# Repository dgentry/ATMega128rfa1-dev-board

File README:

A Better ATMega 128rfa1 Dev Board

See http://www.sparkfun.com/products/9734

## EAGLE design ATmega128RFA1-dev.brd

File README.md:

##A  Better ATMega 128rfa1 Dev Board

See http://www.sparkfun.com/products/9734

Some of the complaints in the comments that I've started to address:

1) If you solder headers into the battery (for hitec connector), ISP,
and uart pins, you won’t be able to insert the ISP programmer
connector – there isn’t any room! If you use this, put your
battery/uart headers underneath your board. A bit silly, but no other
choice.  
[Moved the ISP header left, hopefully gives enough room]

2) With nothing connected but a fully charged 6V battery, this board still has bad voltage drops when turning on the transmitter. You must solder on a capacitor between ground and 3.3V or it won’t work. I put a 20uF tantelum on it, and the resets went away.
<br>[suggested 20uF tantalum in the C5 silkscreen]

4) The traces look like someone used Eagle CAD auto-route and called it a day, without doing much of any touching up.
<br>[Reduced number of vias by about 50%, made antenna signal lines straighter and kept them on top of the board, beefed up power and ground lines where I could]

My suggestion: get rid of the power jack and then by careful redesign a similar board can be made small enough to fit in a breadboard, maybe even cheap enough for some of the people complaining about the high price tag.
<br>[to do, but not sure that'll make it super small anyway]

Oh heck, if any of you guys at SparkFun are listening, here’s my wish-list for a hypothetical future revision of this board:
1) Drop the regulator, or make it an optional DIY addition.
<br>[You're populating your own board, drop away.  :]

2) Make all of the break out pins on the top and bottom aligned to a 0.1" grid.
<br>[All the pins on the side are aligned.  The three connectors at the bottom/end of the board should probably go up, not down]

3) Add a JTAG port in addition to the ISP port. Feel free to use a 0.05" pitch connector for the JTAG port is space is tight.
<br>[to do]

4) Add a U.FL connector (or at least the landing pattern for it) to the board, so that I can solder off the chip antenna and add a Real antenna without too much headache.
<br>[to do]

The result would be a more affordable and more desirable product. I'd by another one. Or two.

Thanks to JÃ¶rg Wunsch on avrfreaks.com, the problem is that the TST
pin is left floating. After connecting this pin to ground, reset and
power on reset works reliably.
<br>[added solderable/cuttable jumper "GND-TST"]

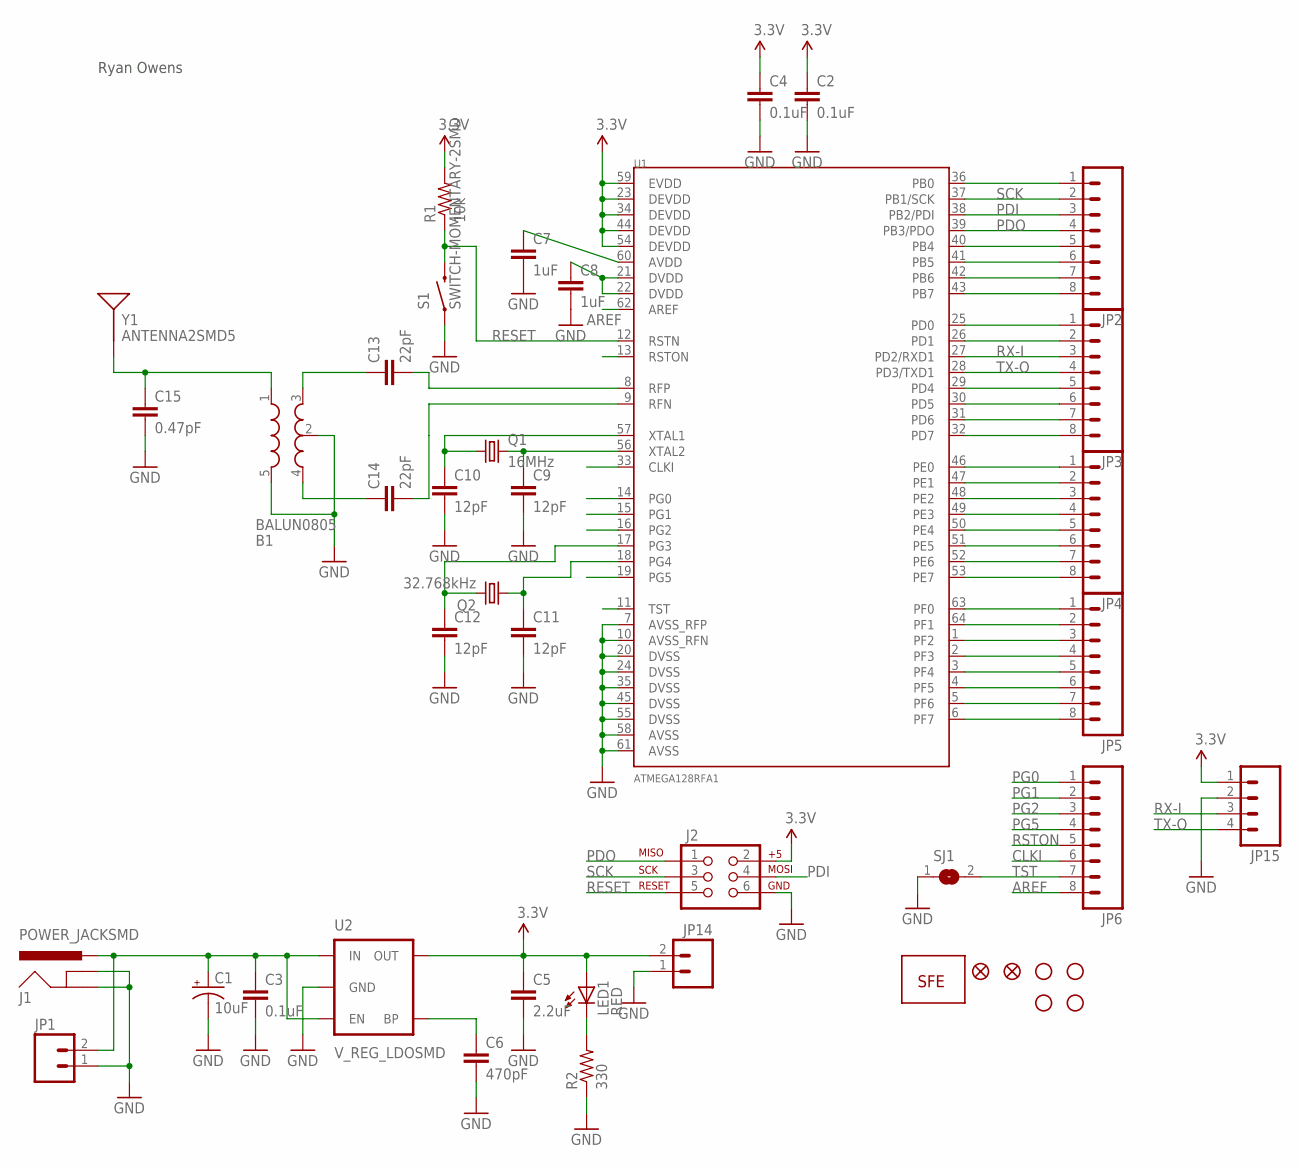
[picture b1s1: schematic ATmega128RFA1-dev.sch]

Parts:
B1: BALUN0805; BALUN
C1: 10uF; EIA3216
C2, C3, C4: 0.1uF; 0603-CAP
C5: 2.2uF; 0603-CAP
C6: 470pF; 0603-CAP
C7, C8: 1uF; 0805
C9, C10, C11, C12: 12pF; 0603-CAP
C13, C14: 22pF; 0603-CAP
C15: 0.47pF; 0603-CAP
J1: POWER_JACKSMD; POWER_JACK_SMD
J2: AVR_SPI_PRG_6PTH; 2X3
JP1, JP14: M02PTH; 1X02
JP2, JP3, JP4, JP5, JP6: M08; 1X08
JP7: LOGO-SFENEW; SFE-NEW-WEBLOGO
JP8, JP9: FIDUCIAL1X2; FIDUCIAL-1X2
JP10, JP11, JP12, JP13: STAND-OFF
JP15: M04PTH; 1X04
LED1: RED; LED-0603
Q1: 16MHz; CRYSTAL-SMD-5X3
Q2: 32.768kHz; CRYSTAL-32KHZ-SMD
R1: 10k; 0603-RES
R2: 330; 0603-RES
S1: SWITCH-MOMENTARY-2SMD; TACTILE_SWITCH_SMD
SJ1: SJ
U1: ATMEGA128RFA1; QFN-64
U2: V_REG_LDOSMD; SOT23-5
Y1: ANTENNA2SMD5; ANTENNA-CHIP5

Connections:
3.3V: C2.1, C4.1, C5.1, J2.2, JP14.2, JP15.1, LED1.A, R1.2, U1.23 (DEVDD), U1.34 (DEVDD), U1.44 (DEVDD), U1.54 (DEVDD), U1.59 (EVDD), U2.5 (OUT)
AREF: JP6.8, U1.62 (AREF)
CLKI: JP6.6, U1.33 (CLKI)
GND: B1.2 (GND), B1.5 (GND), C1.C (-), C2.2, C3.2, C4.2, C5.2, C6.2, C7.2, C8.2, C9.2, C10.2, C11.2, C12.2, C15.2, J1.GND (GNDBREAK), J1.P$4 (GND), J2.6, JP1.1, JP14.1, JP15.2, R2.1, S1.1, SJ1.1, U1.7 (AVSS_RFP), U1.10 (AVSS_RFN), U1.20 (DVSS), U1.24 (DVSS), U1.35 (DVSS), U1.45 (DVSS), U1.55 (DVSS), U1.58 (AVSS), U1.61 (AVSS), U2.2 (GND)
unnamed: B1.3 (OUT1), C13.1
unnamed: B1.4 (OUT2), C14.1
unnamed: C1.A (+), C3.1, J1.VIN0 (PWR), JP1.2, U2.1 (IN), U2.3 (EN)
unnamed: B1.1 (IN), C15.1, Y1.FEED
unnamed: C8.1, U1.21 (DVDD), U1.22 (DVDD)
unnamed: C14.2, U1.9 (RFN)
unnamed: C13.2, U1.8 (RFP)
unnamed: LED1.C, R2.2
unnamed: C7.1, U1.60 (AVDD)
unnamed: C10.1, Q1.1, U1.57 (XTAL1)
unnamed: C9.1, Q1.3 (2), U1.56 (XTAL2)
unnamed: C12.1, Q2.X2 (2), U1.17 (PG3)
unnamed: C11.1, Q2.X1 (1), U1.18 (PG4)
unnamed: C6.1, U2.4 (BP)
unnamed: JP2.1, U1.36 (PB0)
unnamed: JP2.5, U1.40 (PB4)
unnamed: JP2.6, U1.41 (PB5)
unnamed: JP2.7, U1.42 (PB6)
unnamed: JP2.8, U1.43 (PB7)
unnamed: JP3.1, U1.25 (PD0)
unnamed: JP3.2, U1.26 (PD1)
unnamed: JP3.5, U1.29 (PD4)
unnamed: JP3.6, U1.30 (PD5)
unnamed: JP3.7, U1.31 (PD6)
unnamed: JP3.8, U1.32 (PD7)
unnamed: JP4.1, U1.46 (PE0)
unnamed: JP4.2, U1.47 (PE1)
unnamed: JP4.3, U1.48 (PE2)
unnamed: JP4.4, U1.49 (PE3)
unnamed: JP4.5, U1.50 (PE4)
unnamed: JP4.6, U1.51 (PE5)
unnamed: JP4.7, U1.52 (PE6)
unnamed: JP4.8, U1.53 (PE7)
unnamed: JP5.1, U1.63 (PF0)
unnamed: JP5.2, U1.64 (PF1)
unnamed: JP5.3, U1.1 (PF2)
unnamed: JP5.4, U1.2 (PF3)
unnamed: JP5.5, U1.3 (PF4)
unnamed: JP5.6, U1.4 (PF5)
unnamed: JP5.7, U1.5 (PF6)
unnamed: JP5.8, U1.6 (PF7)
PDI: J2.4, JP2.3, U1.38 (PB2/PDI)
PDO: J2.1, JP2.4, U1.39 (PB3/PDO)
PG0: JP6.1, U1.14 (PG0)
PG1: JP6.2, U1.15 (PG1)
PG2: JP6.3, U1.16 (PG2)
PG5: JP6.4, U1.19 (PG5)
RESET: J2.5, R1.1, S1.3 (2), U1.12 (RSTN)
RSTON: JP6.5, U1.13 (RSTON)
RX-I: JP3.3, JP15.3, U1.27 (PD2/RXD1)
SCK: J2.3, JP2.2, U1.37 (PB1/SCK)
TST: JP6.7, SJ1.2, U1.11 (TST)
TX-O: JP3.4, JP15.4, U1.28 (PD3/TXD1)

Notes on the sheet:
Ryan Owens

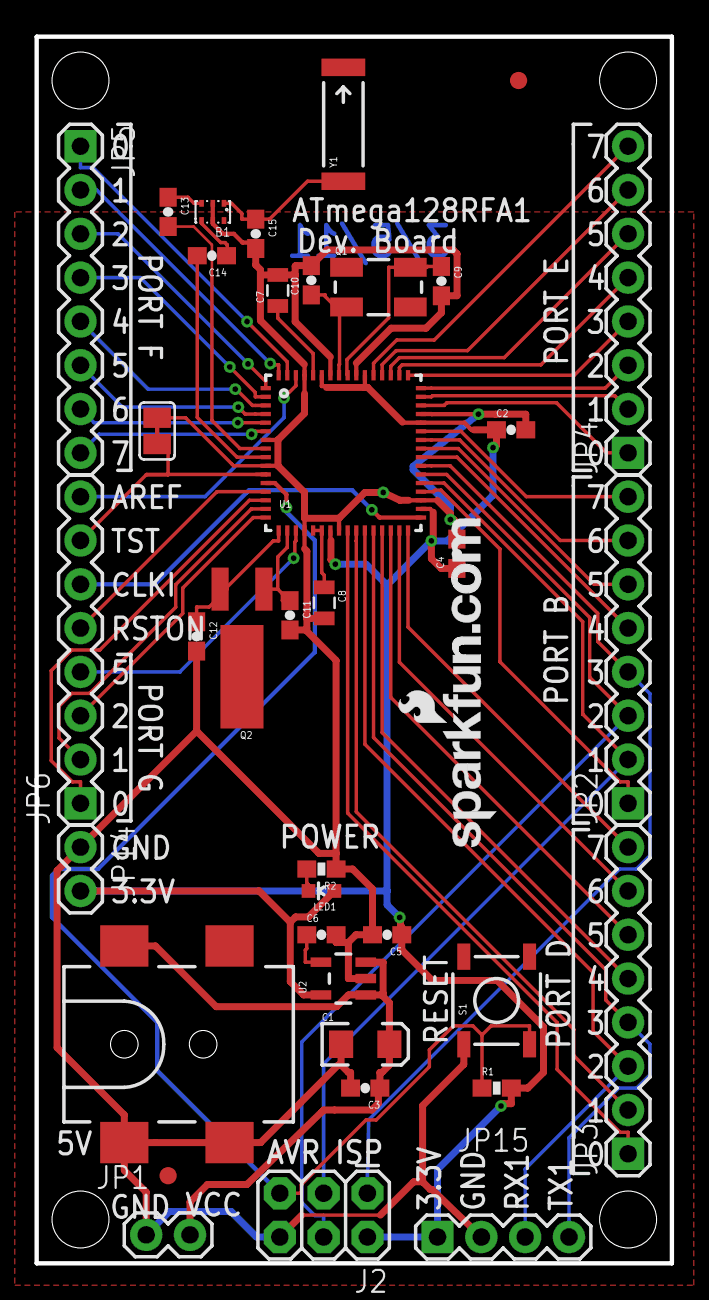
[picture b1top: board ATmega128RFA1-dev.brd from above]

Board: 2 copper layers, 36.8 x 71.1 mm, 43 parts (0 on the bottom side), 57 nets.

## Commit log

2012-02-09 New layout and fixes for Sparkfun's similar board.
2012-02-11 Got rid of extraneous files
2012-03-04 Gave the files more reasonable names
2012-03-04 Updated README.md with issues and status
2012-03-04 Added trace so solder jumper is connected until you cut it.
2012-03-04 Testing formatting
2012-03-04 Anotherformattingtest
2012-03-04 Formatting better yet?
2012-03-04 More dorking withformatting
2012-03-04 Formatting. . .
2012-03-14 Rearranged CC message so more of the board fits on my display
2012-04-13 Include the design rules.

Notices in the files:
ATmega128RFA1-dev.brd:
Creative Commons Attribution
http://creativecommons.org/licenses/by-sa/3.0
